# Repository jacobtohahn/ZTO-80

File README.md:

# ZTO-80
The ZTO-80 is a capable and highly expandable line of Z80 computers and peripherals.

[Hackaday](https://hackaday.io/project/167253-zto-80-modular-computer-system)

## Design
The ZTO-80 is built around the Zilog Z80 CPU, which was designed in 1976. It is still in production today, and, like the 6502, has found its place among hobbyists, particularly within the scope of vintage computing.

The system has two main designs: the SBC and the Modular System.
The ZTO-80 SBC is perfect for those wanting to get started developing with the Z80, both in hardware and software, while the Modular System is built from the ground up to be fully customizable, making it the perfect prototyping environment for more experienced developers.

### SBC
The ZTO-80 Single Board Computer, as the name implies, consists of only one PCB containing all essential system ICs along with I/O. This makes it cheaper and more compact than a multi-board system, with the downside being that it lacks the flexibility and customization it would have otherwise. My design addresses this downside by providing as many on-board features as possible, while allowing customization through configuration headers and an expansion bus.

#### SBC Features:
- CPU: Zilog Z80, running at 4-20MHz (depending on the model and your crystal choice)
- Memory:
  - RAM: 32K
  - ROM: 32K (with optional BASIC interpreter)
- I/O:
  - SIO:
    - Two serial channels with programmable baud rates
  - PIO:
    - Two 8-bit parallel ports, one with a darlington transistor array for high current output
  - CTC:
    - Four timers with external triggers

### Modular System
The ZTO-80 Modular System is a multi-board system allowing ultimate customization and expansion. The system is built out of *modules* and a *backplane*. The modules contain individual pieces of a ZTO-80 computer system (such as the CPU, memory, serial I/O, etc). The backplane provides power and ties all of the modules together. A bus provides a standardized interface for modules to communicate with each other and connect to the backplane.

The main advantage of a modular system is flexiblilty. A user can install or remove individual features, or can create new features in the form of modules. This allows rapid prototyping and troubleshooting. Also, due to increased board space, more customization options can be implemented into individual modules.

Currently, work on the modular system is paused while I finish designing and testing the latest version of the SBC.

#### Official ZTO-80 Modular System modules:
- ZTO-80 Backplane 5
- ZTO-80 CPU
- ZTO-80 Memory
- ZTO-80 SIO
- ZTO-80 PIO (to be designed)
- ZTO-80 CTC

## How I use this repository
This repository keeps all of the PCB files and code for the ZTO-80. To keep things simple for me, I will update this repository each time I make a major change to an aspect of the design, either to the PCB or the code. I will also release minor fixes to the design.

## Contact
If you need to contact me for any reason, the best way is through my email, jtohahn@gmail.com.

You can also try to reach me through a private message on Hackaday.io, but there is no guarantee that I will see it.

## License
Copyright Jacob Hahn 2020.

This source describes Open Hardware and is licensed under the CERN-OHLS v2.
You may redistribute and modify this hardware and make products
using it under the terms of the CERN-OHL-S v2 (https:/cern.ch/cern-ohl).
This hardware is distributed WITHOUT ANY EXPRESS OR IMPLIED
WARRANTY, INCLUDING OF MERCHANTABILITY, SATISFACTORY QUALITY
AND FITNESS FOR A PARTICULAR PURPOSE. Please see the CERN-OHL-S v2
for applicable conditions.

Source location: https://github.com/jacobtohahn/ZTO-80

This documentation is released under the Attribution-ShareAlike 4.0 International License and is copyright Jacob Hahn 2020. You may use and share this documentation under the terms of the license, found here: https://creativecommons.org/licenses/by-sa/4.0/.

Please note that the CC-BY-SA License only applies to this project's documentation. Any other files, such as design files, are licensed under the terms of the CERN-OHL-S v2 license, as described above.

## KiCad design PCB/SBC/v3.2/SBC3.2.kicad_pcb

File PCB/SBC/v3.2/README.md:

# ZTO-80 SBC
This folder contains all the KiCad files for ZTO-80 SBC v3.2, along with an additional files and documentation.

This folder is a work in progress. The Getting Started guide has not been created yet. Check back soon!

## Additional files and subdirectories
- **PDF**: A subdirectory containing PDF files of the schematic and PCB.
- **Getting Started with the ZTO-80 SBC v3.2.pdf**: A getting started guide for the SBC v3.2.

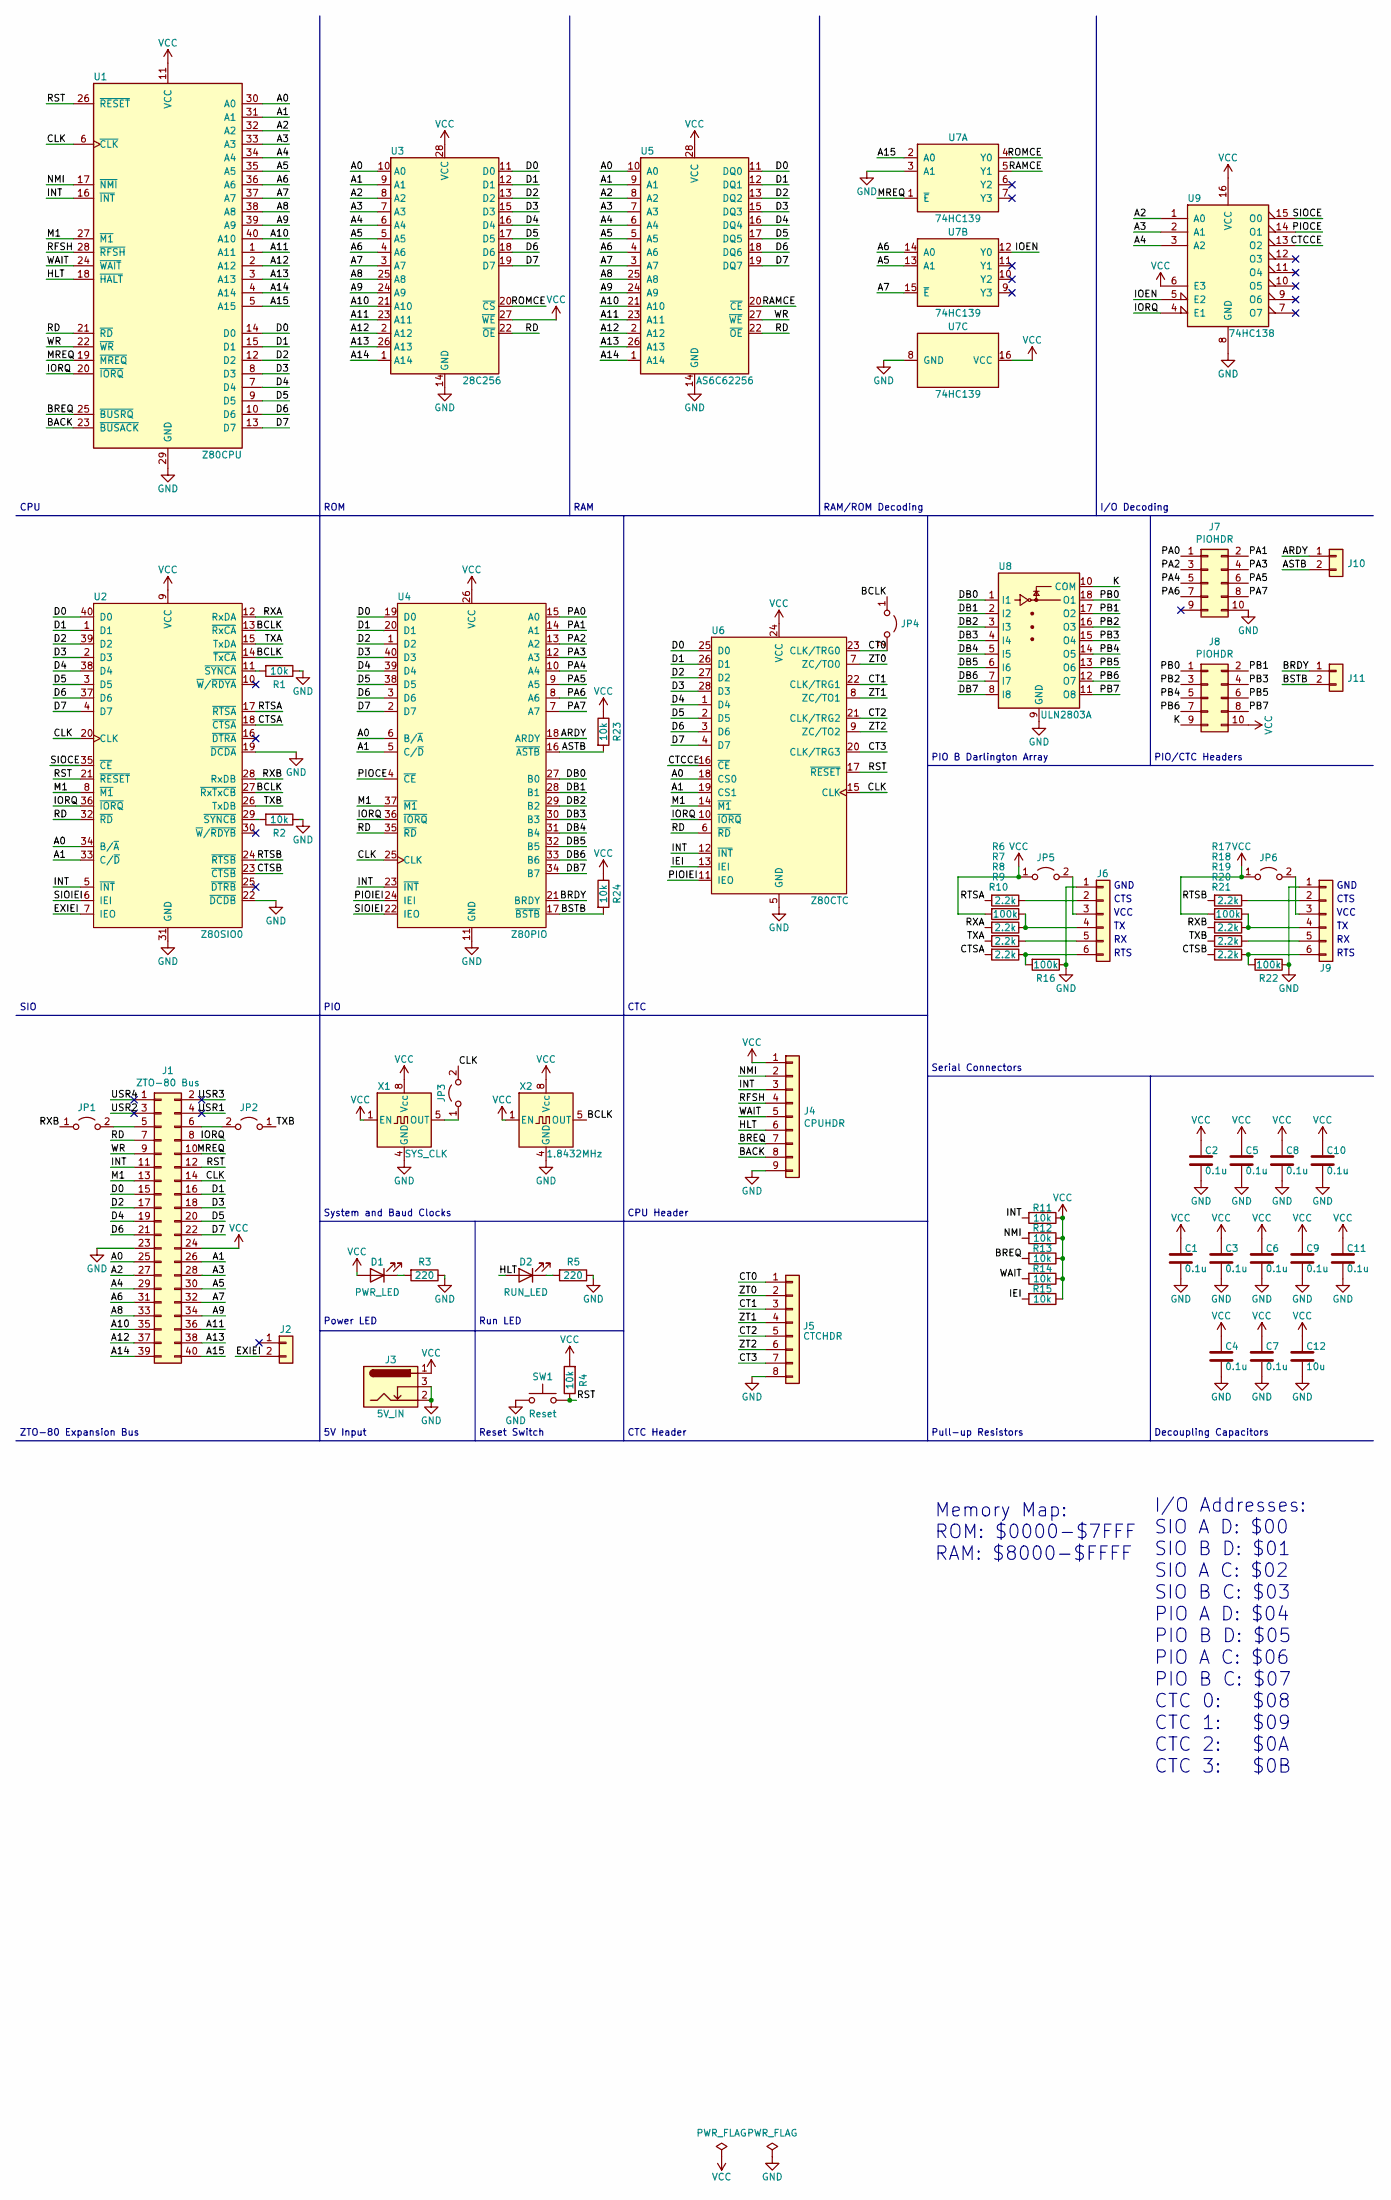
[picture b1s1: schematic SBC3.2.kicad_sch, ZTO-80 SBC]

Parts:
C1, C2, C3, C4, C5, C6, C7, C8, C9, C10, C11: 0.1u; C_0805_2012Metric_Pad1.15x1.40mm_HandSolder
C12: 10u; C_0805_2012Metric_Pad1.15x1.40mm_HandSolder
D1: PWR_LED; LED_D3.0mm
D2: RUN_LED; LED_D3.0mm
J1: ZTO-80 Bus; PinHeader_2x20_P2.54mm_Vertical
J2, J10, J11: Conn_01x02; PinHeader_1x02_P2.54mm_Vertical
J3: 5V_IN; BarrelJack_CUI_PJ-102A_Horizontal
J4: CPUHDR; PinHeader_1x09_P2.54mm_Vertical
J5: CTCHDR; PinHeader_1x08_P2.54mm_Vertical
J6, J9: SIOHDR; PinHeader_1x06_P2.54mm_Vertical
J7, J8: PIOHDR; PinHeader_2x05_P2.54mm_Vertical
JP1, JP2, JP3, JP4, JP5, JP6: Jumper_2_Open; PinHeader_1x02_P2.54mm_Vertical
R1, R2, R4, R11, R12, R13, R14, R15, R23, R24: 10k; R_0805_2012Metric_Pad1.15x1.40mm_HandSolder
R3, R5: 220; R_0805_2012Metric_Pad1.15x1.40mm_HandSolder
R6, R8, R9, R10, R17, R19, R20, R21: 2.2k; R_0805_2012Metric_Pad1.15x1.40mm_HandSolder
R7, R16, R18, R22: 100k; R_0805_2012Metric_Pad1.15x1.40mm_HandSolder
SW1: Reset; SW_PUSH_6mm
U1: Z80CPU; DIP-40_W15.24mm
U2: Z80SIO0; DIP-40_W15.24mm
U3: 28C256; DIP-28_W15.24mm
U4: Z80PIO; DIP-40_W15.24mm
U5: AS6C62256; DIP-28_W15.24mm
U6: Z80CTC; DIP-28_W15.24mm
U7: 74HC139; DIP-16_W7.62mm
U8: ULN2803A; DIP-18_W7.62mm
U9: 74HC138; DIP-16_W7.62mm
X1: SYS_CLK; Oscillator_DIP-8
X2: 1.8432MHz; Oscillator_DIP-8

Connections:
/A0: J1.25, U1.30 (A0), U2.34 (B/~A), U3.10 (A0), U4.6 (B/~A), U5.10 (A0), U6.18 (CS0)
/A1: J1.26, U1.31 (A1), U2.33 (C/~D), U3.9 (A1), U4.5 (C/~D), U5.9 (A1), U6.19 (CS1)
/A2: J1.27, U1.32 (A2), U3.8 (A2), U5.8 (A2), U9.1 (A0)
/A3: J1.28, U1.33 (A3), U3.7 (A3), U5.7 (A3), U9.2 (A1)
/A4: J1.29, U1.34 (A4), U3.6 (A4), U5.6 (A4), U9.3 (A2)
/A5: J1.30, U1.35 (A5), U3.5 (A5), U5.5 (A5), U7.13 (A1)
/A6: J1.31, U1.36 (A6), U3.4 (A6), U5.4 (A6), U7.14 (A0)
/A7: J1.32, U1.37 (A7), U3.3 (A7), U5.3 (A7), U7.15 (~E)
/A8: J1.33, U1.38 (A8), U3.25 (A8), U5.25 (A8)
/A9: J1.34, U1.39 (A9), U3.24 (A9), U5.24 (A9)
/A10: J1.35, U1.40 (A10), U3.21 (A10), U5.21 (A10)
/A11: J1.36, U1.1 (A11), U3.23 (A11), U5.23 (A11)
/A12: J1.37, U1.2 (A12), U3.2 (A12), U5.2 (A12)
/A13: J1.38, U1.3 (A13), U3.26 (A13), U5.26 (A13)
/A14: J1.39, U1.4 (A14), U3.1 (A14), U5.1 (A14)
/A15: J1.40, U1.5 (A15), U7.2 (A0)
/ARDY: J10.1, U4.18 (ARDY)
/ASTB: J10.2, R23.2, U4.16 (~ASTB)
/BACK: J4.8, U1.23 (~BUSACK)
/BCLK: JP4.1 (A), U2.13 (~RxCA), U2.14 (~TxCA), U2.27 (~RxTxCB), X2.5 (OUT)
/BRDY: J11.1, U4.21 (BRDY)
/BREQ: J4.7, R13.2, U1.25 (~BUSRQ)
/BSTB: J11.2, R24.2, U4.17 (~BSTB)
/CLK: J1.14, JP3.2 (B), U1.6 (~CLK), U2.20 (CLK), U4.25 (CLK), U6.15 (CLK)
/CT0: J5.1, JP4.2 (B), U6.23 (CLK/TRG0)
/CT1: J5.3, U6.22 (CLK/TRG1)
/CT2: J5.5, U6.21 (CLK/TRG2)
/CT3: J5.7, U6.20 (CLK/TRG3)
/CTCCE: U6.16 (~CE), U9.13 (O2)
/CTSA: R10.2, U2.18 (~CTSA)
/CTSB: R21.2, U2.23 (~CTSB)
/D0: J1.15, U1.14 (D0), U2.40 (D0), U3.11 (D0), U4.19 (D0), U5.11 (DQ0), U6.25 (D0)
/D1: J1.16, U1.15 (D1), U2.1 (D1), U3.12 (D1), U4.20 (D1), U5.12 (DQ1), U6.26 (D1)
/D2: J1.17, U1.12 (D2), U2.39 (D2), U3.13 (D2), U4.1 (D2), U5.13 (DQ2), U6.27 (D2)
/D3: J1.18, U1.8 (D3), U2.2 (D3), U3.15 (D3), U4.40 (D3), U5.15 (DQ3), U6.28 (D3)
/D4: J1.19, U1.7 (D4), U2.38 (D4), U3.16 (D4), U4.39 (D4), U5.16 (DQ4), U6.1 (D4)
/D5: J1.20, U1.9 (D5), U2.3 (D5), U3.17 (D5), U4.38 (D5), U5.17 (DQ5), U6.2 (D5)
/D6: J1.21, U1.10 (D6), U2.37 (D6), U3.18 (D6), U4.3 (D6), U5.18 (DQ6), U6.3 (D6)
/D7: J1.22, U1.13 (D7), U2.4 (D7), U3.19 (D7), U4.2 (D7), U5.19 (DQ7), U6.4 (D7)
/DB0: U4.27 (B0), U8.1 (I1)
/DB1: U4.28 (B1), U8.2 (I2)
/DB2: U4.29 (B2), U8.3 (I3)
/DB3: U4.30 (B3), U8.4 (I4)
/DB4: U4.31 (B4), U8.5 (I5)
/DB5: U4.32 (B5), U8.6 (I6)
/DB6: U4.33 (B6), U8.7 (I7)
/DB7: U4.34 (B7), U8.8 (I8)
/EXIEI: J2.2, U2.7 (IEO)
/HLT: D2.2 (A), J4.6, U1.18 (~HALT)
/IEI: R15.2, U6.13 (IEI)
/INT: J1.11, J4.3, R11.2, U1.16 (~INT), U2.5 (~INT), U4.23 (~INT), U6.12 (~INT)
/IOEN: U7.12 (Y0), U9.5 (E2)
/IORQ: J1.8, U1.20 (~IORQ), U2.36 (~IORQ), U4.36 (~IORQ), U6.10 (~IORQ), U9.4 (E1)
/K: J8.9, U8.10 (COM)
/M1: J1.13, U1.27 (~M1), U2.8 (~M1), U4.37 (~M1), U6.14 (~M1)
/MREQ: J1.10, U1.19 (~MREQ), U7.1 (~E)
/NMI: J4.2, R12.2, U1.17 (~NMI)
/PA0: J7.1, U4.15 (A0)
/PA1: J7.2, U4.14 (A1)
/PA2: J7.3, U4.13 (A2)
/PA3: J7.4, U4.12 (A3)
/PA4: J7.5, U4.10 (A4)
/PA5: J7.6, U4.9 (A5)
/PA6: J7.7, U4.8 (A6)
/PA7: J7.8, U4.7 (A7)
/PB0: J8.1, U8.18 (O1)
/PB1: J8.2, U8.17 (O2)
/PB2: J8.3, U8.16 (O3)
/PB3: J8.4, U8.15 (O4)
/PB4: J8.5, U8.14 (O5)
/PB5: J8.6, U8.13 (O6)
/PB6: J8.7, U8.12 (O7)
/PB7: J8.8, U8.11 (O8)
/PIOCE: U4.4 (~CE), U9.14 (O1)
/PIOIEI: U4.24 (IEI), U6.11 (IEO)
/RAMCE: U5.20 (~CE), U7.5 (Y1)
/RD: J1.7, U1.21 (~RD), U2.32 (~RD), U3.22 (~OE), U4.35 (~RD), U5.22 (~OE), U6.6 (~RD)
/RFSH: J4.4, U1.28 (~RFSH)
/ROMCE: U3.20 (~CS), U7.4 (Y0)
/RST: J1.12, R4.1, SW1.2, U1.26 (~RESET), U2.21 (~RESET), U6.17 (~RESET)
/RTSA: R6.2, U2.17 (~RTSA)
/RTSB: R17.2, U2.24 (~RTSB)
/RXA: R8.2, U2.12 (RxDA)
/RXB: JP1.1 (A), R19.2, U2.28 (RxDB)
/SIOCE: U2.35 (~CE), U9.15 (O0)
/SIOIEI: U2.6 (IEI), U4.22 (IEO)
/TXA: R9.2, U2.15 (TxDA)
/TXB: JP2.1 (A), R20.2, U2.26 (TxDB)
/USR1: J1.4
/USR2: J1.3
/USR3: J1.2
/USR4: J1.1
/WAIT: J4.5, R14.2, U1.24 (~WAIT)
/WR: J1.9, U1.22 (~WR), U5.27 (~WE)
/ZT0: J5.2, U6.7 (ZC/TO0)
/ZT1: J5.4, U6.8 (ZC/TO1)
/ZT2: J5.6, U6.9 (ZC/TO2)
GND: C1.2, C2.2, C3.2, C4.2, C5.2, C6.2, C7.2, C8.2, C9.2, C10.2, C11.2, C12.2, J1.23, J3.2, J3.3, J4.9, J5.8, J6.1, J7.10, J9.1, R1.1, R2.1, R3.1, R5.1, R16.1, R22.1, SW1.1, U1.29 (GND), U2.19 (~DCDA), U2.22 (~DCDB), U2.31 (GND), U3.14 (GND), U4.11 (GND), U5.14 (GND), U6.5 (GND), U7.3 (A1), U7.8 (GND), U8.9 (GND), U9.8 (GND), X1.4 (GND), X2.4 (GND); also elsewhere on the board
unnamed: D1.1 (K), R3.2
unnamed: D2.1 (K), R5.2
unnamed: J1.5, JP1.2 (B)
unnamed: J1.6, JP2.2 (B)
unnamed: J6.2, R6.1
unnamed: J6.3, JP5.2 (B)
unnamed: J6.4, R7.1, R8.1
unnamed: J6.5, R9.1
unnamed: J6.6, R10.1, R16.2
unnamed: J9.2, R17.1
unnamed: J9.3, JP6.2 (B)
unnamed: J9.4, R18.1, R19.1
unnamed: J9.5, R20.1
unnamed: J9.6, R21.1, R22.2
unnamed: JP3.1 (A), X1.5 (OUT)
unnamed: R1.2, U2.11 (~SYNCA)
unnamed: R2.2, U2.29 (~SYNCB)
VCC: C1.1, C2.1, C3.1, C4.1, C5.1, C6.1, C7.1, C8.1, C9.1, C10.1, C11.1, C12.1, D1.2 (A), J1.24, J3.1, J4.1, J8.10, JP5.1 (A), JP6.1 (A), R4.2, R7.2, R11.1, R12.1, R13.1, R14.1, R15.1, R18.2, R23.1, R24.1, U1.11 (VCC), U2.9 (VCC), U3.27 (~WE), U3.28 (VCC), U4.26 (VCC), U5.28 (VCC), U6.24 (VCC), U7.16 (VCC), U9.6 (E3), U9.16 (VCC), X1.1 (EN), X1.8 (Vcc), X2.1 (EN), X2.8 (Vcc)

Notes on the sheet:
Reset Switch
SIO
ZTO-80 Expansion Bus
PIO
PIO B Darlington Array
Decoupling Capacitors
RAM
Serial Connectors
ROM
CTC Header
CTS
Run LED
5V Input
I/O Addresses: SIO A D: $00 SIO B D: $01 SIO A C: $02 SIO B C: $03 PIO A D: $04 PIO B D: $05 PIO A C: $06 PIO B C: $07 CTC 0: $08 CTC 1: $09 CTC 2: $0A CTC 3: $0B
RAM/ROM Decoding
CPU
Memory Map: ROM: $0000-$7FFF RAM: $8000-$FFFF
CTC
Pull-up Resistors
GND
VCC
Power LED
System and Baud Clocks
RTS
I/O Decoding
PIO/CTC Headers
CPU Header

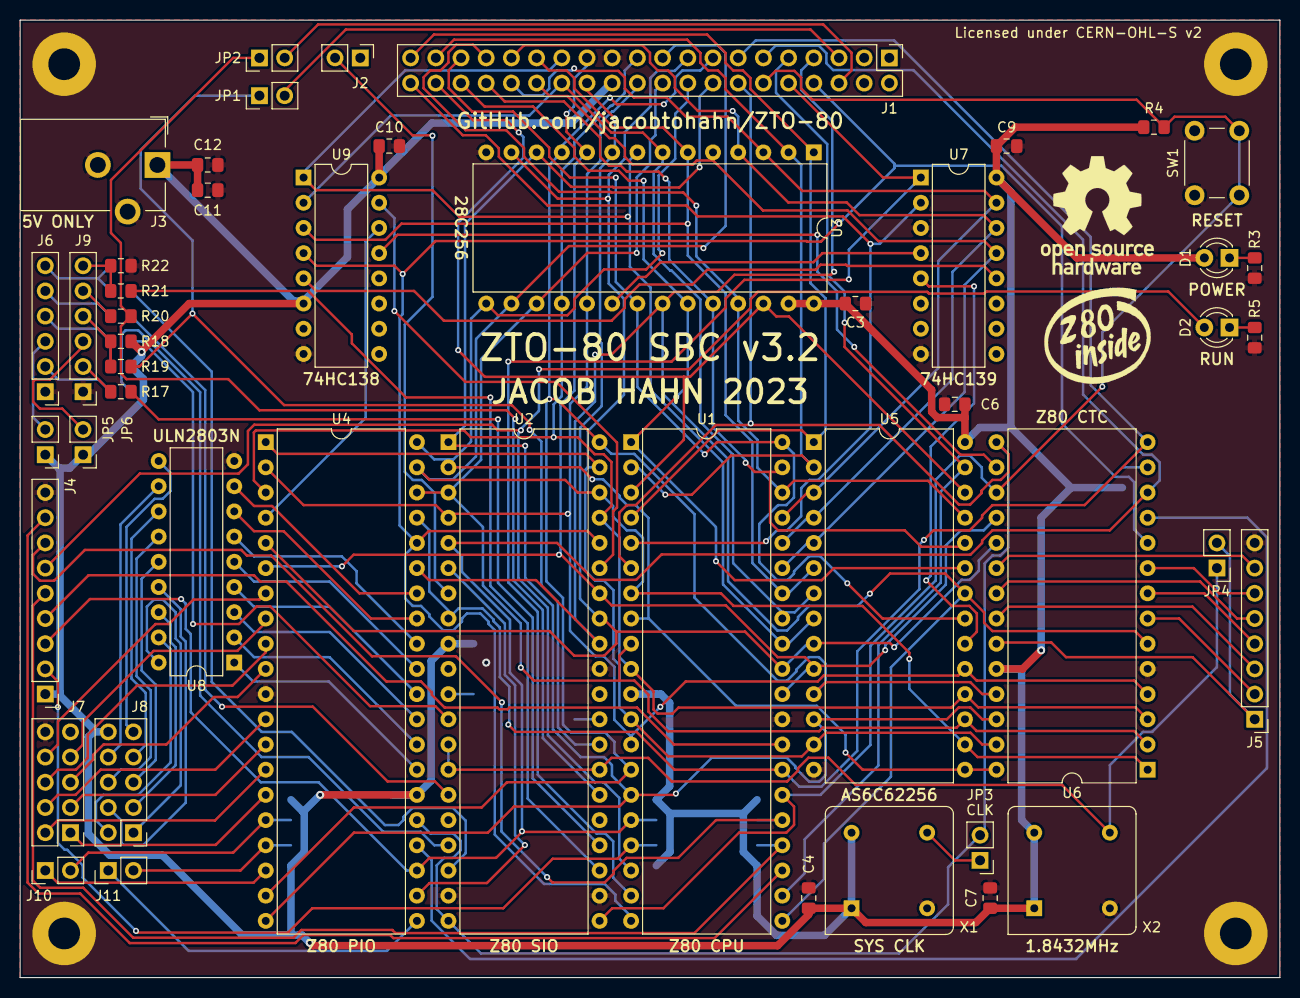
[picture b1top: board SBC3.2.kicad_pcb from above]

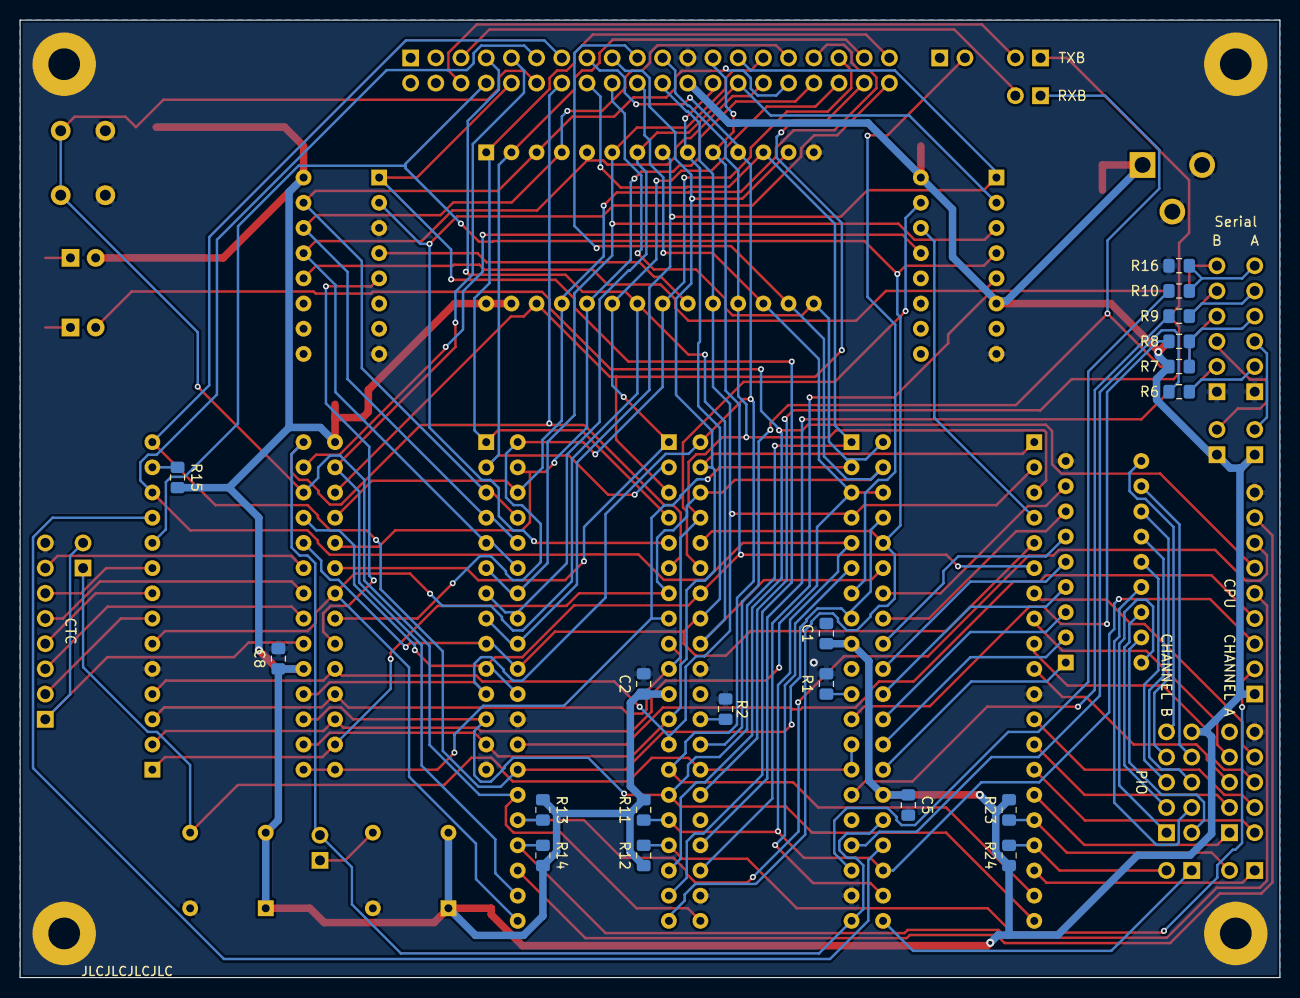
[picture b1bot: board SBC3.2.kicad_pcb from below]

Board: 2 copper layers, 127.0 x 96.5 mm, 71 parts (19 on the bottom side), 112 nets.

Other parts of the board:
Mount1, Mount2, Mount3, Mount4: MountingHole_3.2mm_M3_Pad

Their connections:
GND: Mount1.1, Mount2.1, Mount3.1, Mount4.1; also elsewhere on the board

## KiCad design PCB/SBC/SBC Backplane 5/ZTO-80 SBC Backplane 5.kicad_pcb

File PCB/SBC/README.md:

# ZTO-80 SBC
This folder contains all the KiCad files for the ZTO-80 SBC, along with an additional files and documentation.

Please note that this board has never been manufactured and is simply a prototype. If you would like to make one yourself, be sure to completely examine the schematic for errors. I will make one myself soon to check for errors.

## Additional files and subdirectories
- **SBC_BOM.csv**: A CSV file containing the Bill of Materials for all the parts required to build the SBC.
- **PDF**: A subdirectory containing PDF files of the schematic and PCB.
- **Getting Started with the ZTO-80 SBC.pdf**: A getting started guide for the SBC.

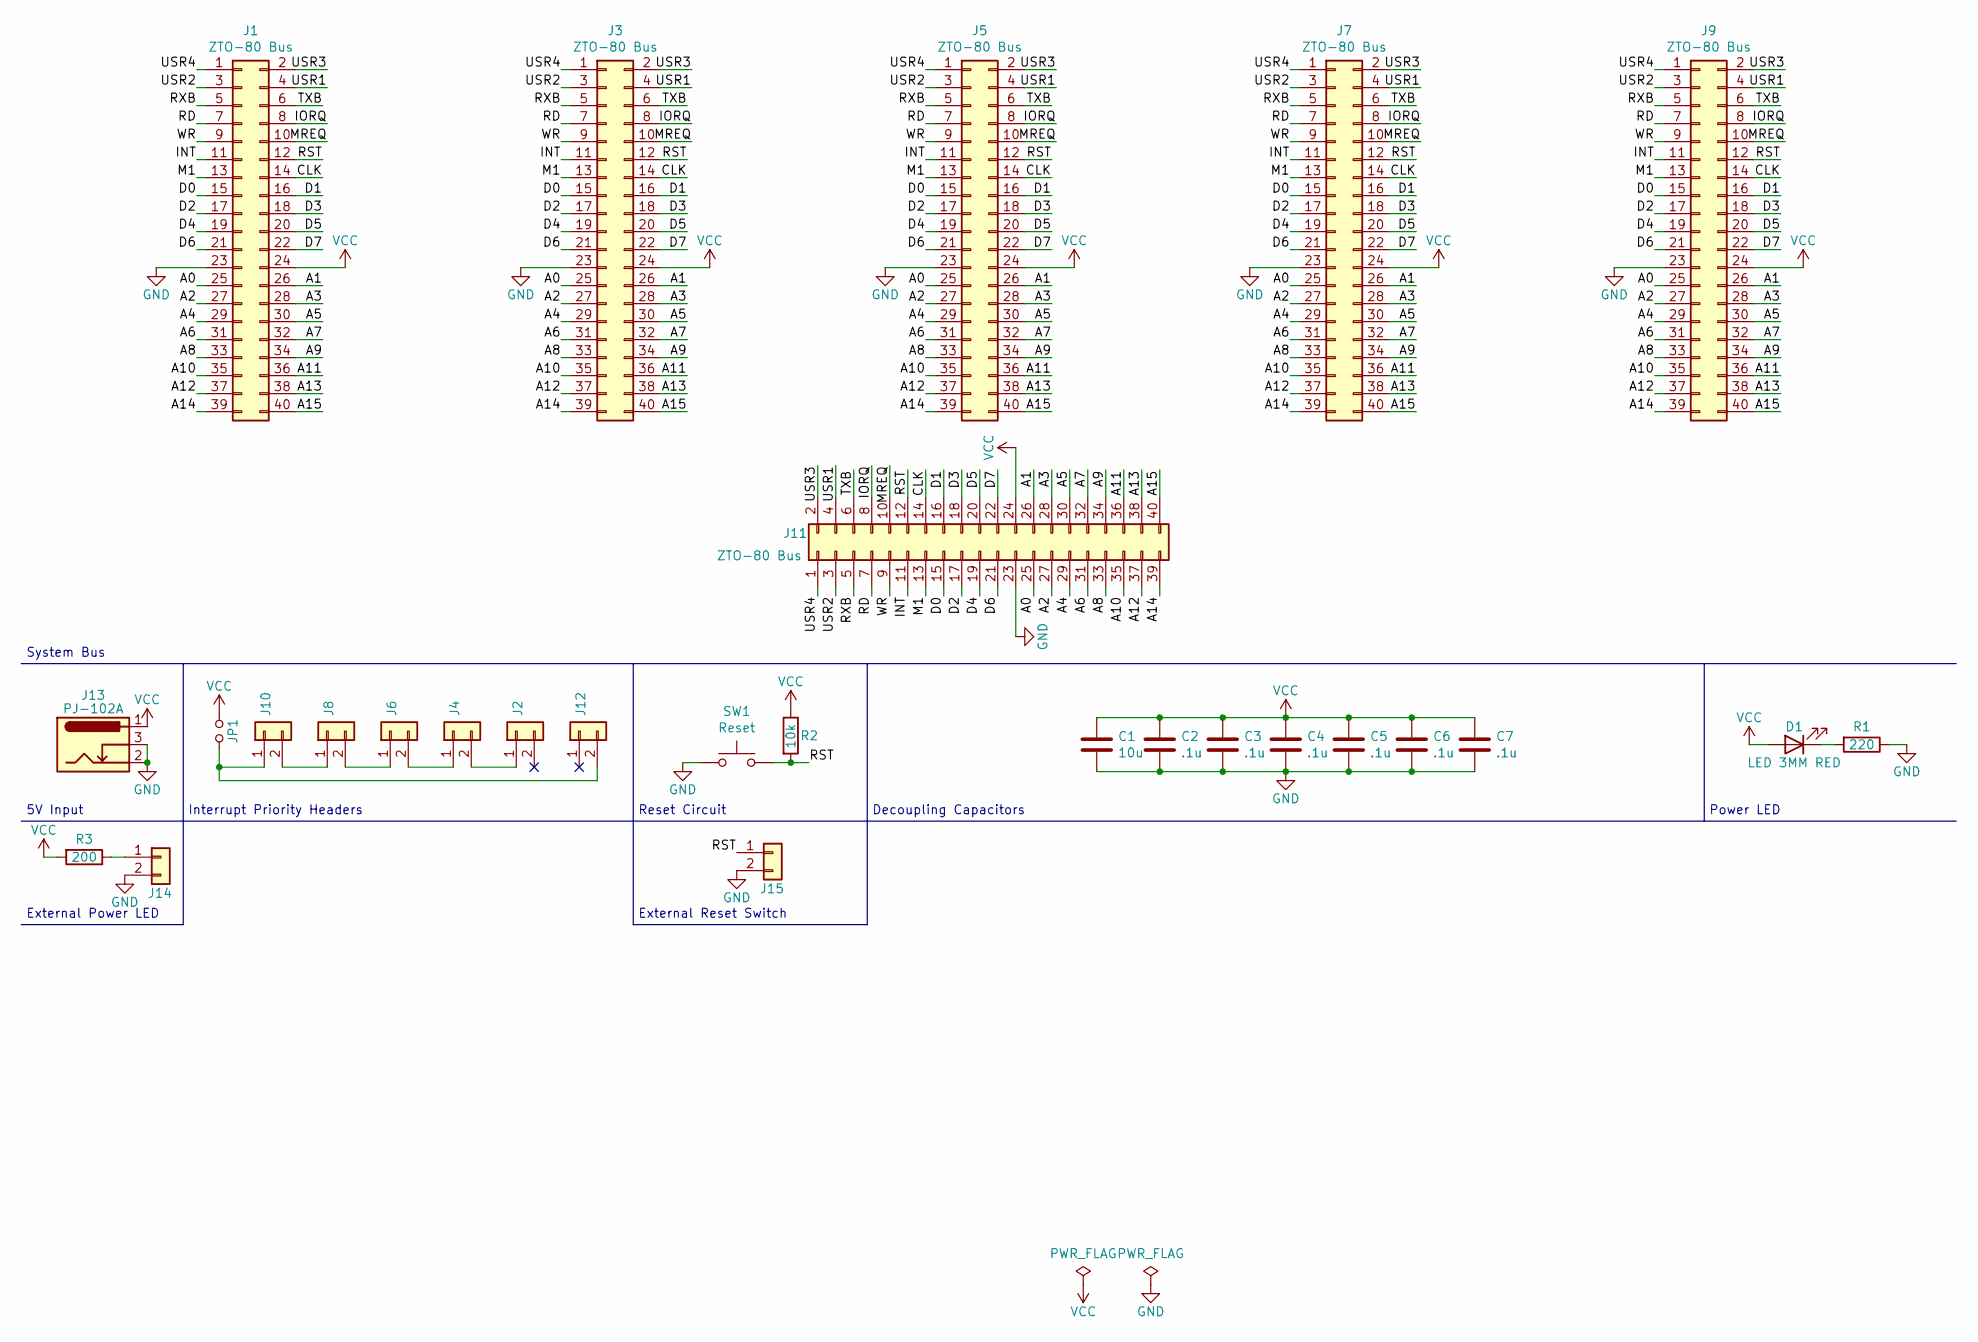
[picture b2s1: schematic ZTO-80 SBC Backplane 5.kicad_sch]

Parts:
C1: 10u; C_0805_2012Metric_Pad1.15x1.40mm_HandSolder
C2, C3, C4, C5, C6, C7: .1u; C_0805_2012Metric_Pad1.15x1.40mm_HandSolder
D1: LED 3MM RED; LED_D3.0mm
J1, J3, J5, J7, J9, J11: ZTO-80 Bus; PinSocket_2x20_P2.54mm_Vertical
J2, J4, J6, J8, J10, J12: Conn_01x02; PinSocket_2x01_P2.54mm_Vertical
J13: PJ-102A; BarrelJack_CUI_PJ-102A_Horizontal
J14, J15: Conn_01x02; PinHeader_1x02_P2.54mm_Vertical
JP1: Jumper_NO_Small; PinHeader_1x02_P2.54mm_Vertical
R1: 220; R_0805_2012Metric_Pad1.15x1.40mm_HandSolder
R2: 10k; R_0805_2012Metric_Pad1.15x1.40mm_HandSolder
R3: 200; R_0805_2012Metric_Pad1.15x1.40mm_HandSolder
SW1: Reset; SW_PUSH_6mm

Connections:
/A0: J1.25, J3.25, J5.25, J7.25, J9.25, J11.25
/A1: J1.26, J3.26, J5.26, J7.26, J9.26, J11.26
/A2: J1.27, J3.27, J5.27, J7.27, J9.27, J11.27
/A3: J1.28, J3.28, J5.28, J7.28, J9.28, J11.28
/A4: J1.29, J3.29, J5.29, J7.29, J9.29, J11.29
/A5: J1.30, J3.30, J5.30, J7.30, J9.30, J11.30
/A6: J1.31, J3.31, J5.31, J7.31, J9.31, J11.31
/A7: J1.32, J3.32, J5.32, J7.32, J9.32, J11.32
/A8: J1.33, J3.33, J5.33, J7.33, J9.33, J11.33
/A9: J1.34, J3.34, J5.34, J7.34, J9.34, J11.34
/A10: J1.35, J3.35, J5.35, J7.35, J9.35, J11.35
/A11: J1.36, J3.36, J5.36, J7.36, J9.36, J11.36
/A12: J1.37, J3.37, J5.37, J7.37, J9.37, J11.37
/A13: J1.38, J3.38, J5.38, J7.38, J9.38, J11.38
/A14: J1.39, J3.39, J5.39, J7.39, J9.39, J11.39
/A15: J1.40, J3.40, J5.40, J7.40, J9.40, J11.40
/CLK: J1.14, J3.14, J5.14, J7.14, J9.14, J11.14
/D0: J1.15, J3.15, J5.15, J7.15, J9.15, J11.15
/D1: J1.16, J3.16, J5.16, J7.16, J9.16, J11.16
/D2: J1.17, J3.17, J5.17, J7.17, J9.17, J11.17
/D3: J1.18, J3.18, J5.18, J7.18, J9.18, J11.18
/D4: J1.19, J3.19, J5.19, J7.19, J9.19, J11.19
/D5: J1.20, J3.20, J5.20, J7.20, J9.20, J11.20
/D6: J1.21, J3.21, J5.21, J7.21, J9.21, J11.21
/D7: J1.22, J3.22, J5.22, J7.22, J9.22, J11.22
/INT: J1.11, J3.11, J5.11, J7.11, J9.11, J11.11
/IORQ: J1.8, J3.8, J5.8, J7.8, J9.8, J11.8
/M1: J1.13, J3.13, J5.13, J7.13, J9.13, J11.13
/MREQ: J1.10, J3.10, J5.10, J7.10, J9.10, J11.10
/RD: J1.7, J3.7, J5.7, J7.7, J9.7, J11.7
/RST: J1.12, J3.12, J5.12, J7.12, J9.12, J11.12, J15.1, R2.2, SW1.2
/RXB: J1.5, J3.5, J5.5, J7.5, J9.5, J11.5
/TXB: J1.6, J3.6, J5.6, J7.6, J9.6, J11.6
/USR1: J1.4, J3.4, J5.4, J7.4, J9.4, J11.4
/USR2: J1.3, J3.3, J5.3, J7.3, J9.3, J11.3
/USR3: J1.2, J3.2, J5.2, J7.2, J9.2, J11.2
/USR4: J1.1, J3.1, J5.1, J7.1, J9.1, J11.1
/WR: J1.9, J3.9, J5.9, J7.9, J9.9, J11.9
GND: C1.2, C2.2, C3.2, C4.2, C5.2, C6.2, C7.2, J1.23, J3.23, J5.23, J7.23, J9.23, J11.23, J13.2, J13.3, J14.2, J15.2, R1.1, SW1.1
unnamed: D1.1 (K), R1.2
unnamed: J2.1, J4.2
unnamed: J4.1, J6.2
unnamed: J6.1, J8.2
unnamed: J10.1, J12.2, JP1.2
unnamed: J8.1, J10.2
unnamed: J14.1, R3.1
VCC: C1.1, C2.1, C3.1, C4.1, C5.1, C6.1, C7.1, D1.2 (A), J1.24, J3.24, J5.24, J7.24, J9.24, J11.24, J13.1, JP1.1, R2.1, R3.2

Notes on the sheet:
Power LED
External Reset Switch
System Bus
External Power LED
Interrupt Priority Headers
5V Input
Decoupling Capacitors
Reset Circuit

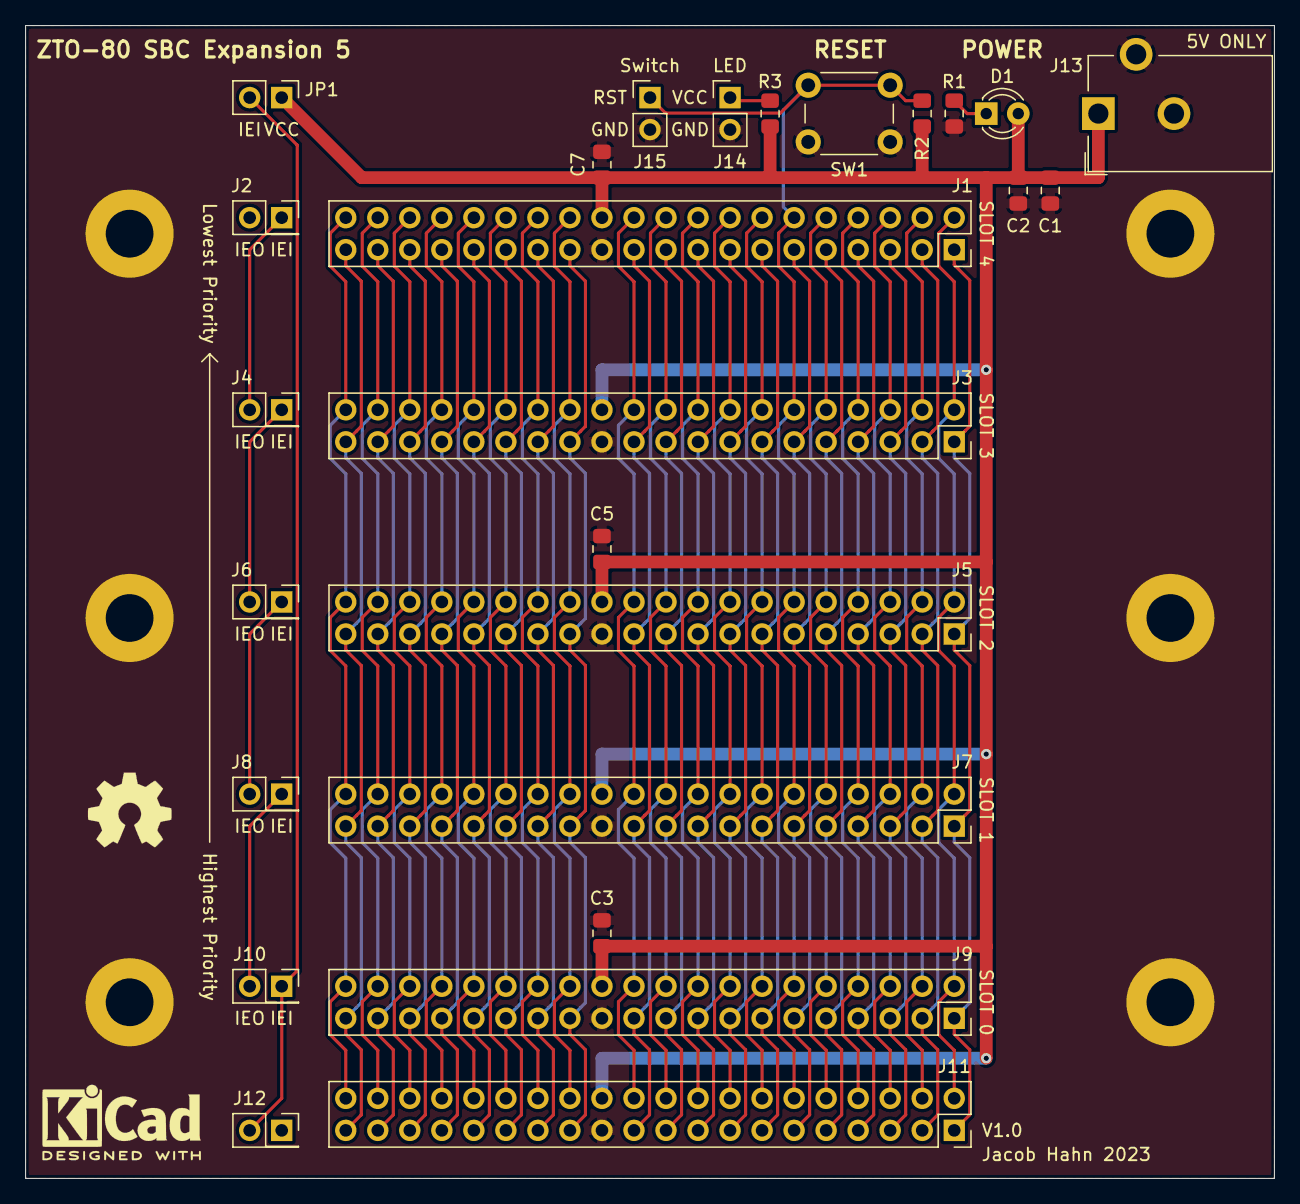
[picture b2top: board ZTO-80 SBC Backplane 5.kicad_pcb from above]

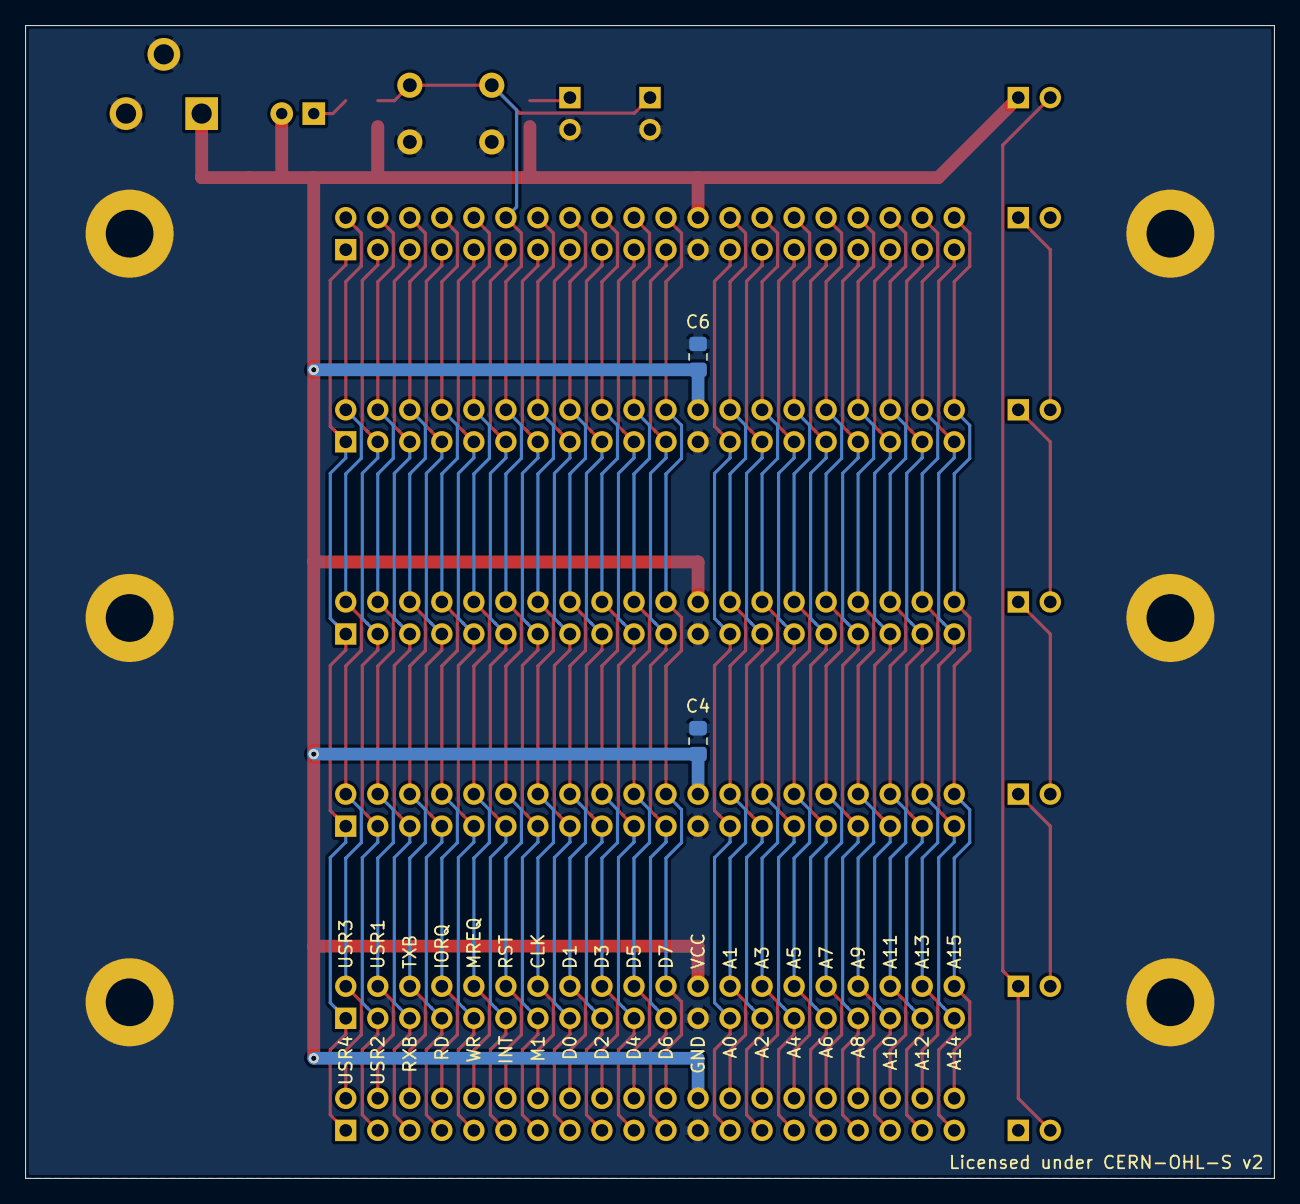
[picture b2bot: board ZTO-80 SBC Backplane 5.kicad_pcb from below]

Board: 2 copper layers, 99.1 x 91.4 mm, 28 parts (2 on the bottom side), 47 nets.

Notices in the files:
PCB/Modular System/ZTO-80 CPU/ZTO-80 CPU.kicad_pcb:
Licensed under CERN-OHL-S v2
